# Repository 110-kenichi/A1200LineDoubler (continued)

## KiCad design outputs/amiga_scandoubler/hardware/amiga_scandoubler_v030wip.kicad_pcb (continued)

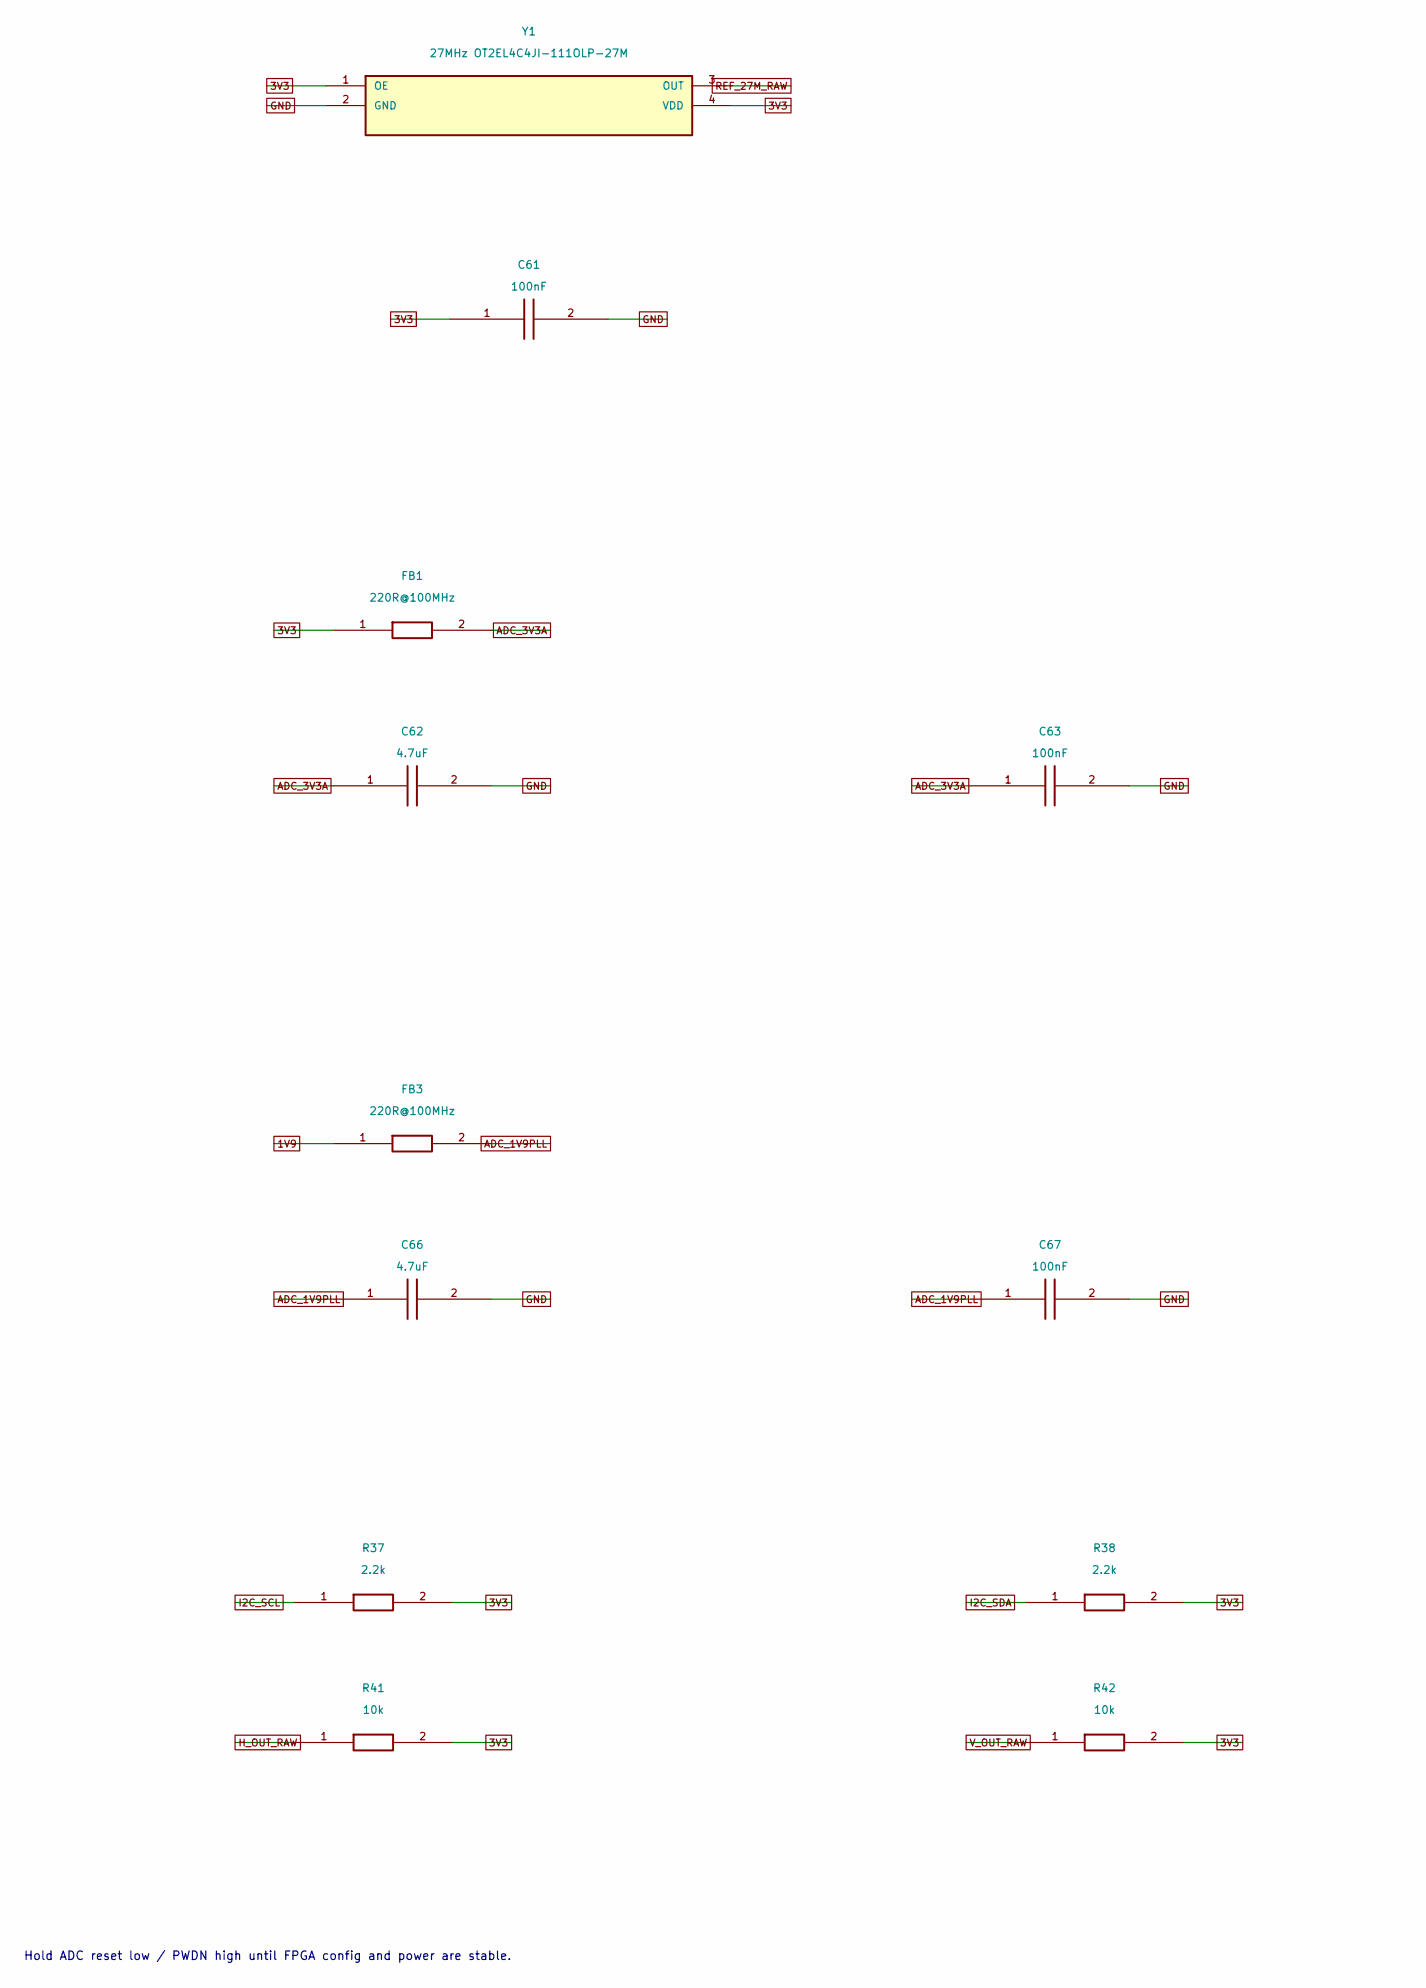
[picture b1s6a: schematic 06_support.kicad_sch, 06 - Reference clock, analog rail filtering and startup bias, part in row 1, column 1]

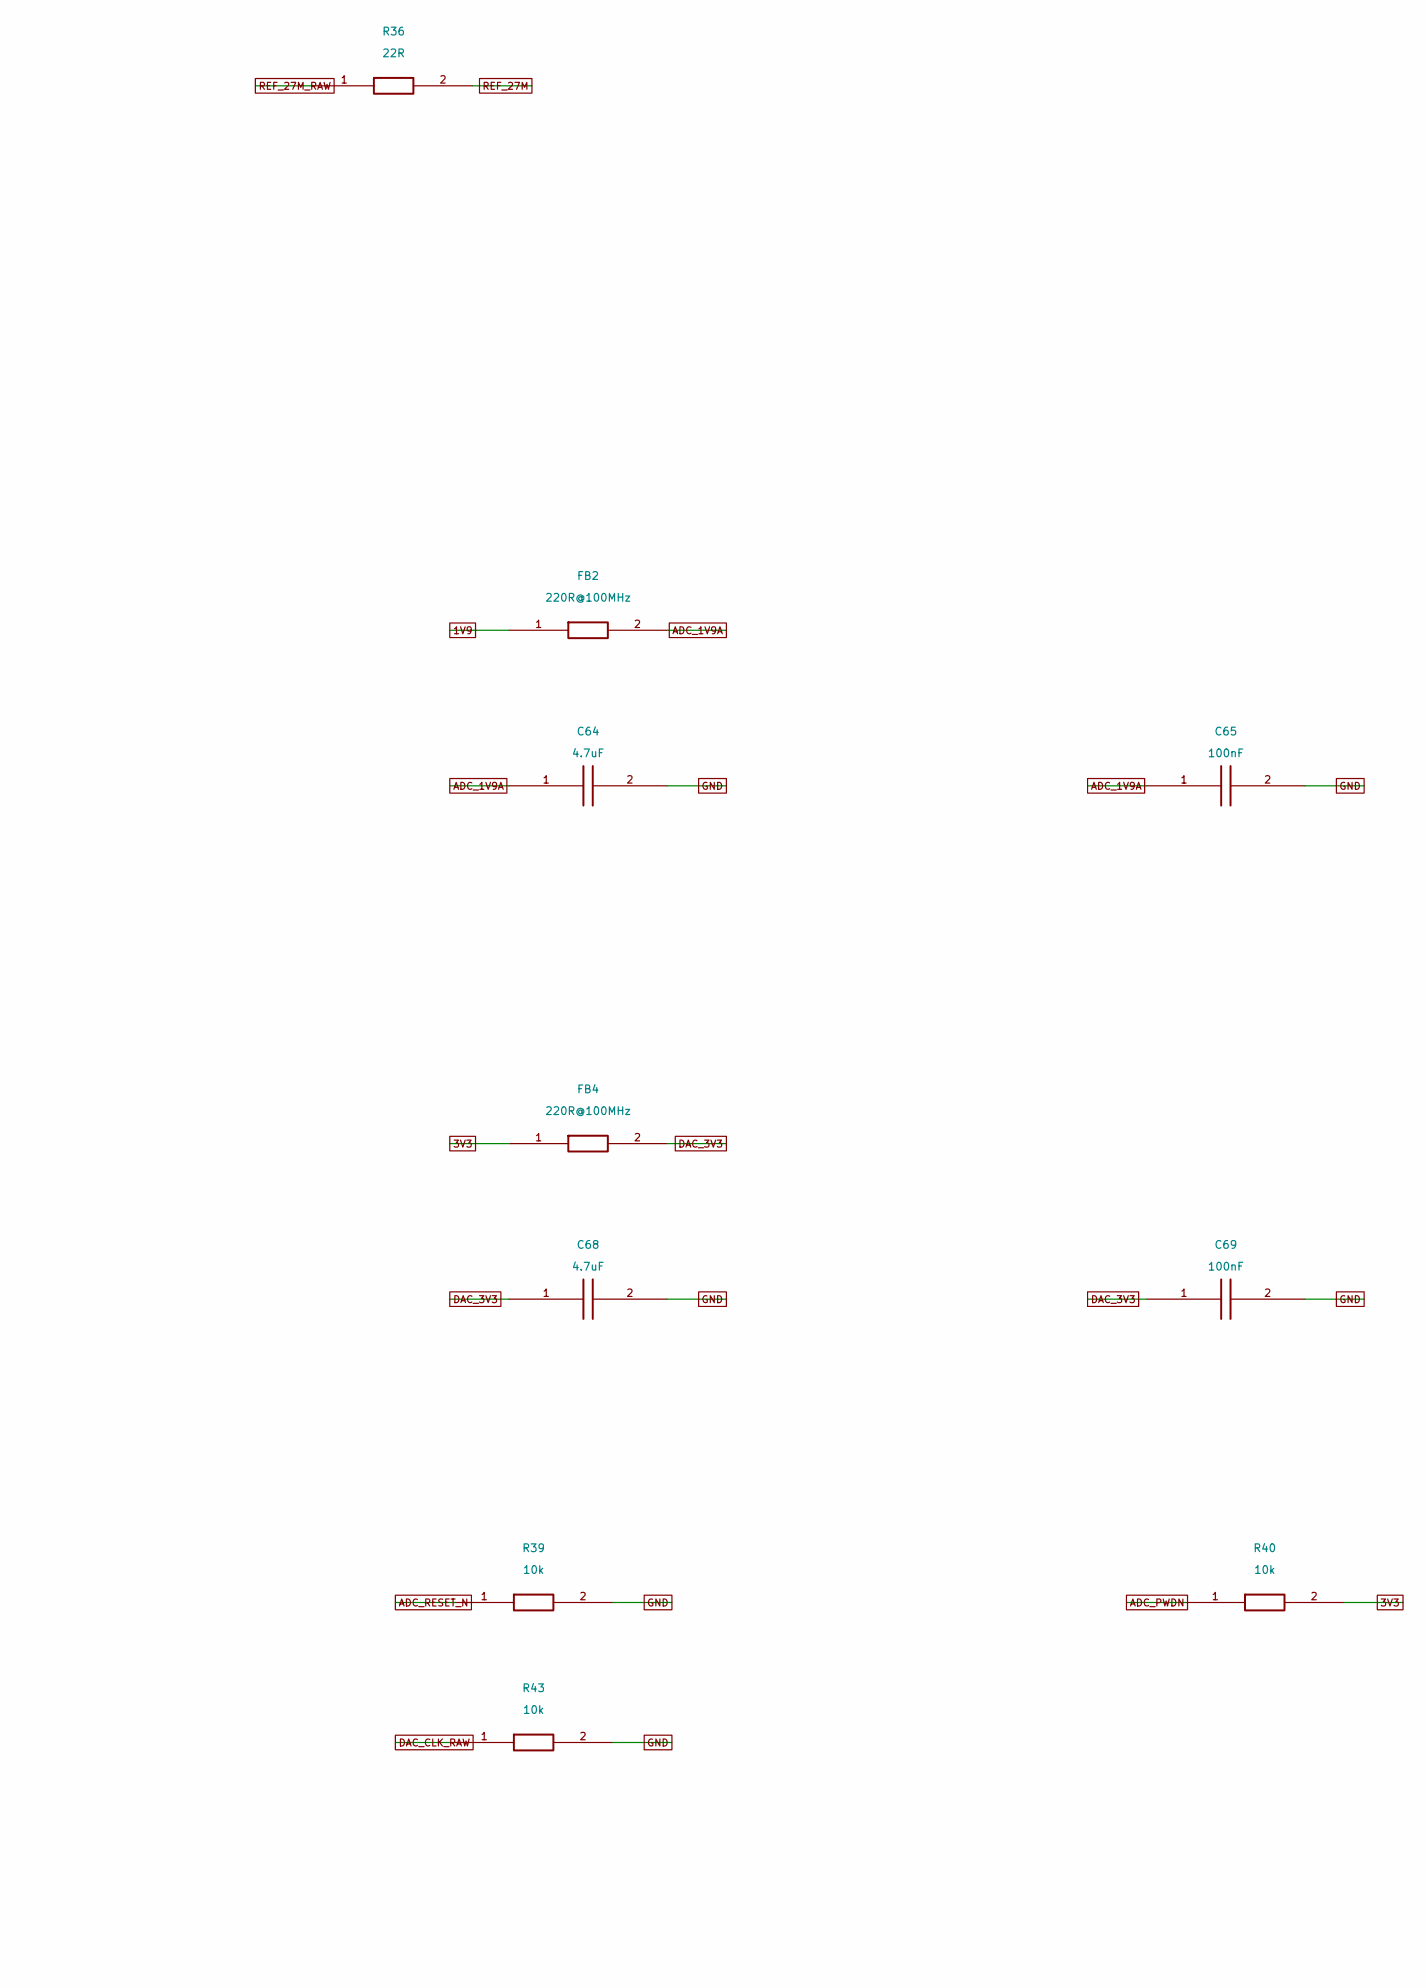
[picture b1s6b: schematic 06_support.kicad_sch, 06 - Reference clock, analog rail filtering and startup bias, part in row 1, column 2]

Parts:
C61, C63, C65, C67, C69: 100nF; C_0603_1608Metric; MPN CC0603KRX7R9BB104; LCSC C14663
C62, C64, C66, C68: 4.7uF; C_0805_2012Metric; MPN CL21A475KAQNNNE; LCSC C1779
FB1, FB2, FB3, FB4: 220R@100MHz; L_0603_1608Metric; MPN HCB1608KF-221T20; LCSC C304314
R36: 22R; R_0603_1608Metric; MPN 0603WAF220JT5E; LCSC C23345
R37, R38: 2.2k; R_0402_1005Metric; MPN 0402WGF2201TCE; LCSC C25879
R39, R40: 10k; R_0402_1005Metric; MPN 0402WGF1002TCE; LCSC C25744
R41, R42, R43: 10k; R_0603_1608Metric; MPN 0603WAF1002T5E; LCSC C25804
Y1: 27MHz OT2EL4C4JI-111OLP-27M; OSC_ECS-3225MVLC_3.2x2.5; MPN OT2EL4C4JI-111OLP-27M; LCSC C5203549

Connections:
1V9: FB2.1, FB3.1; also elsewhere on the board
3V3: C61.1, FB1.1, FB4.1, R37.2, R38.2, R40.2, R41.2, R42.2, Y1.1 (OE), Y1.4 (VDD); also elsewhere on the board
ADC_1V9A: C64.1, C65.1, FB2.2; also elsewhere on the board
ADC_1V9PLL: C66.1, C67.1, FB3.2; also elsewhere on the board
ADC_3V3A: C62.1, C63.1, FB1.2; also elsewhere on the board
ADC_PWDN: R40.1; also elsewhere on the board
ADC_RESET_N: R39.1; also elsewhere on the board
DAC_3V3: C68.1, C69.1, FB4.2; also elsewhere on the board
DAC_CLK_RAW: R43.1; also elsewhere on the board
GND: C61.2, C62.2, C63.2, C64.2, C65.2, C66.2, C67.2, C68.2, C69.2, R39.2, R43.2, Y1.2 (GND); also elsewhere on the board
H_OUT_RAW: R41.1; also elsewhere on the board
I2C_SCL: R37.1; also elsewhere on the board
I2C_SDA: R38.1; also elsewhere on the board
REF_27M: R36.2; also elsewhere on the board
REF_27M_RAW: R36.1, Y1.3 (OUT)
V_OUT_RAW: R42.1; also elsewhere on the board

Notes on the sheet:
Hold ADC reset low / PWDN high until FPGA config and power are stable.

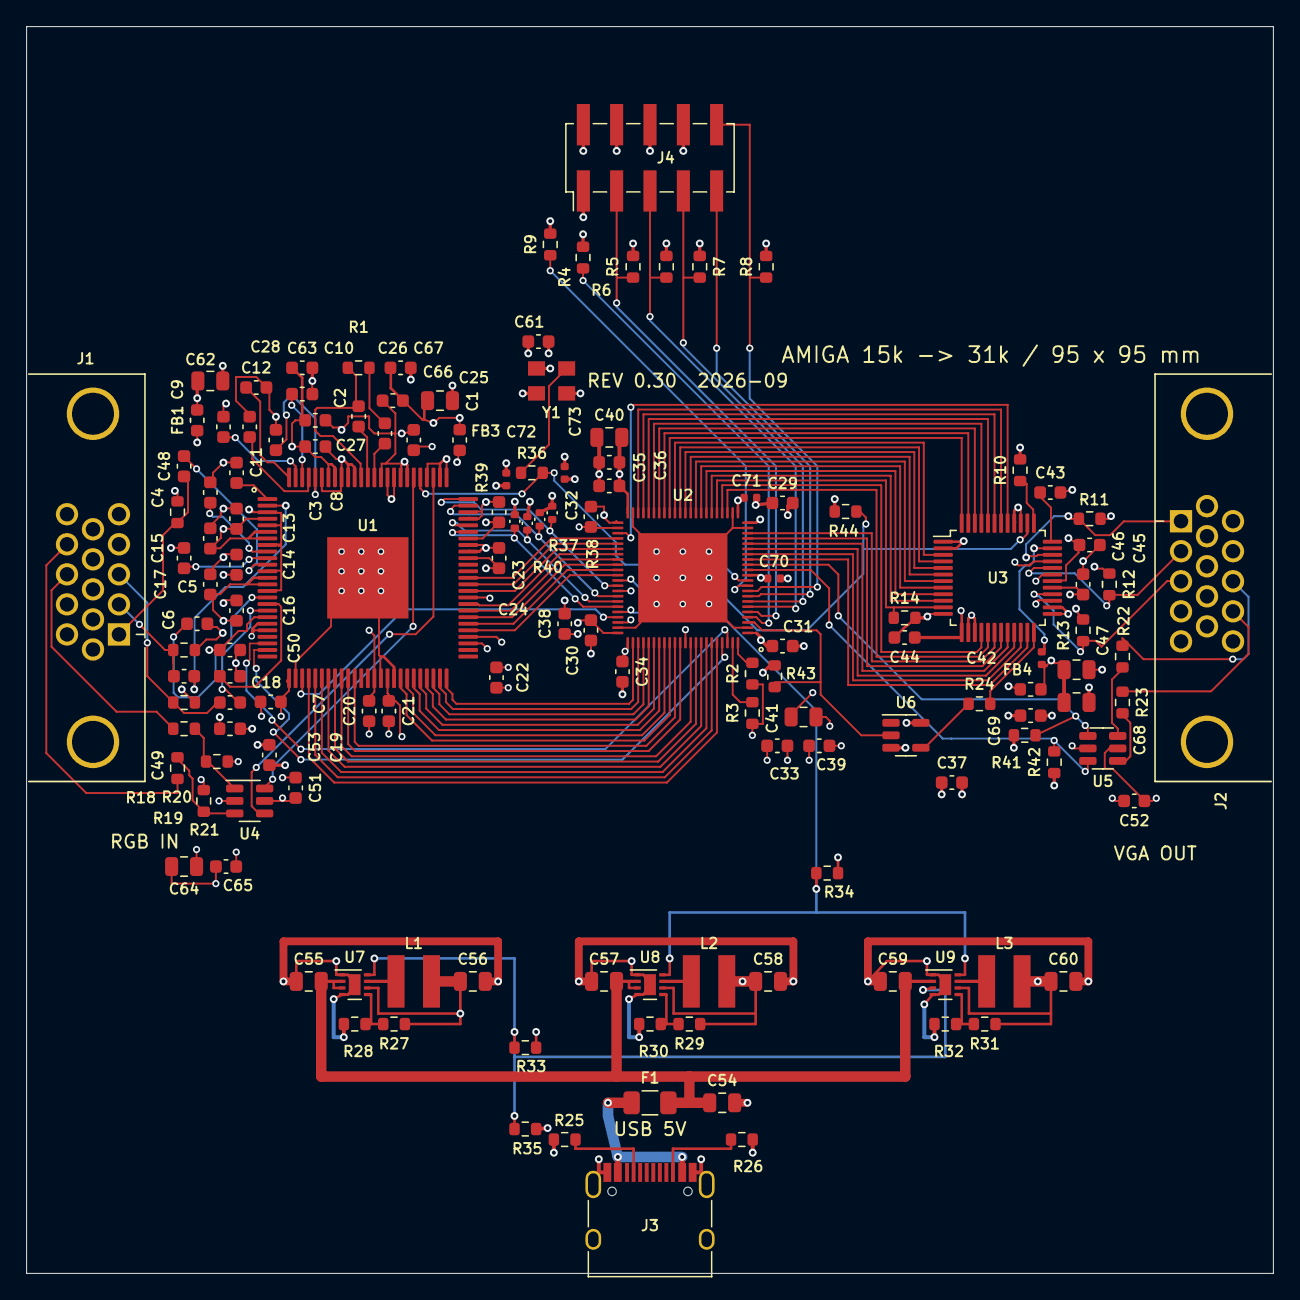
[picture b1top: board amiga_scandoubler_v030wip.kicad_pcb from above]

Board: 4 copper layers, 95.0 x 95.0 mm, 139 parts (0 on the bottom side), 129 nets.

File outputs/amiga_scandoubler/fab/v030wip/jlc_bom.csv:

Comment,Designator,Footprint,LCSC Part #,MPN
100nF,"C1,C13,C14,C15,C16,C17,C18,C19,C20,C21,C22,C23,C24,C25,C26,C27,C28,C29,C30,C31,C32,C33,C34,C35,C36,C37,C38,C39,C43,C44,C45,C46,C48,C49,C50,C51,C52,C53,C61,C63,C65,C67,C69",C_0603_1608Metric,C14663,CC0603KRX7R9BB104
4.7nF,C2,C_0603_1608Metric,C576818,CC0603JRNPO9BN472
1nF,"C3,C9,C11",C_0603_1608Metric,C106246,CC0603JRNPO9BN102
10nF,"C4,C5,C6,C7,C8,C10,C12",C_0603_1608Metric,C85973,GRM1885C1H103JA01D
4.7uF,"C40,C41,C62,C64,C66,C68",C_0805_2012Metric,C1779,CL21A475KAQNNNE
100nF,"C42,C70,C71,C72,C73",C_0402_1005Metric,C1525,CL05B104KO5NNNC
10uF 25V,"C47,C54,C55,C57,C59",C_0805_2012Metric,C15850,CL21A106KAYNNNE
22uF 10V,"C56,C58,C60",C_0805_2012Metric,C45783,CL21A226MAQNNNE
1A hold - select,F1,Fuse_1206_3216Metric,C269119,SMD1206B110TFT
220R@100MHz,"FB1,FB2,FB3,FB4",L_0603_1608Metric,C304314,HCB1608KF-221T20
HYC06-HDR15B-060,"J1,J2",DE15_HOAUC_HYC06-HDR15B-060,C711364,HYC06-HDR15B-060
TYPE-C-31-M-12,J3,USB_C_Receptacle_HRO_TYPE-C-31-M-12_Slot0.8,C165948,TYPE-C-31-M-12
JTAG 2x05 2.54mm,J4,PinHeader_2x05_P2.54mm_Vertical_SMD,C32713285,HX PZ2.54-2x5P TP
2.2uH,"L1,L2,L3",L_TDK_VLS4012CX,C92959,NRS4018T2R2MDGJ
1.5k,R1,R_0603_1608Metric,C22843,0603WAF1501T5E
4.7k,"R2,R3,R4,R5,R6,R7,R8,R9,R44",R_0603_1608Metric,C23162,0603WAF4701T5E
536R 0.1%,R10,R_0603_1608Metric,C861466,RT0603BRD07536RL
75R 0.1%,"R11,R12,R13,R15,R16,R17",R_0603_1608Metric,C319466,AR03BTCX0750
10k,"R14,R33,R34,R41,R42,R43",R_0603_1608Metric,C25804,0603WAF1002T5E
33R,"R18,R20,R22,R23",R_0603_1608Metric,C23140,0603WAF330JT5E
100k,"R19,R21,R35",R_0603_1608Metric,C25803,0603WAF1003T5E
22R,"R24,R36",R_0603_1608Metric,C23345,0603WAF220JT5E
5.1k 1%,"R25,R26",R_0603_1608Metric,C23186,0603WAF5101T5E
312k 0.1%,R27,R_0603_1608Metric,C861315,RT0603BRD07312KL
100k 0.1%,"R28,R30,R32",R_0603_1608Metric,C122538,RT0603BRD07100KL
137k 0.1%,R29,R_0603_1608Metric,C861114,RT0603BRD07137KL
49.9k 0.1%,R31,R_0603_1608Metric,C705780,RT0603BRD0749K9L
2.2k,"R37,R38",R_0402_1005Metric,C25879,0402WGF2201TCE
10k,"R39,R40",R_0402_1005Metric,C25744,0402WGF1002TCE
TVP7002PZP,U1,TQFP-100_TVP7002_14x14_P0.5_EP6.2,C3824085,TVP7002PZP
GW1N-LV4QN88C6/I5,U2,QFN-88_GW1N4_10x10_P0.4_EP6.8,C31900351,GW1N-LV4QN88C6/I5
ADV7125KSTZ140,U3,LQFP-48_7x7mm_P0.5mm,C9668,ADV7125KSTZ140
SN74LVC2G17DBVR,"U4,U5",SOT-23-6,C19829674,SN74LVC2G17DBVR
SN74LVC1G17DBVR,U6,SOT-23-5,C7836,SN74LVC1G17DBVR
TPS62160DSGR,"U7,U8,U9",WSON-8-1EP_2x2mm_P0.5mm_EP0.9x1.6mm,C324077,TPS62160DSGR
27MHz OT2EL4C4JI-111OLP-27M,Y1,OSC_ECS-3225MVLC_3.2x2.5,C5203549,OT2EL4C4JI-111OLP-27M
